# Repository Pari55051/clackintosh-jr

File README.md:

# Clackintosh Jr.
A macropad to accompany my mac and my keyboard 'Clackintosh'

## Features
- 8 mechanical keys
- Rotary encoder for volume up/down _ its switch as mute button
- 0.91" SSD1306 OLED display
- per-key RGB light
- Xiao RP2040 and KMK firmware

Each key launches a different app on macOS, the rotary encoder controls volume, and the OLED provides live feedback.

## Screenshots

## BOM

| Item                               | Qty |
|------------------------------------|-----|
| Seeed Xiao RP2040                  | 1   |
| Mechanical switches                | 8   |
| Keycaps                            | 8   |
| EC11Rotary Encoder                 | 1   |
| 0.91" OLED display                 | 1   |
| Diodes (for matrix)                | 9   |
| PCB                                | 1   |
| 3D printed case (top + bottom)     | 1   |
| Screws (case)                      | 4   |

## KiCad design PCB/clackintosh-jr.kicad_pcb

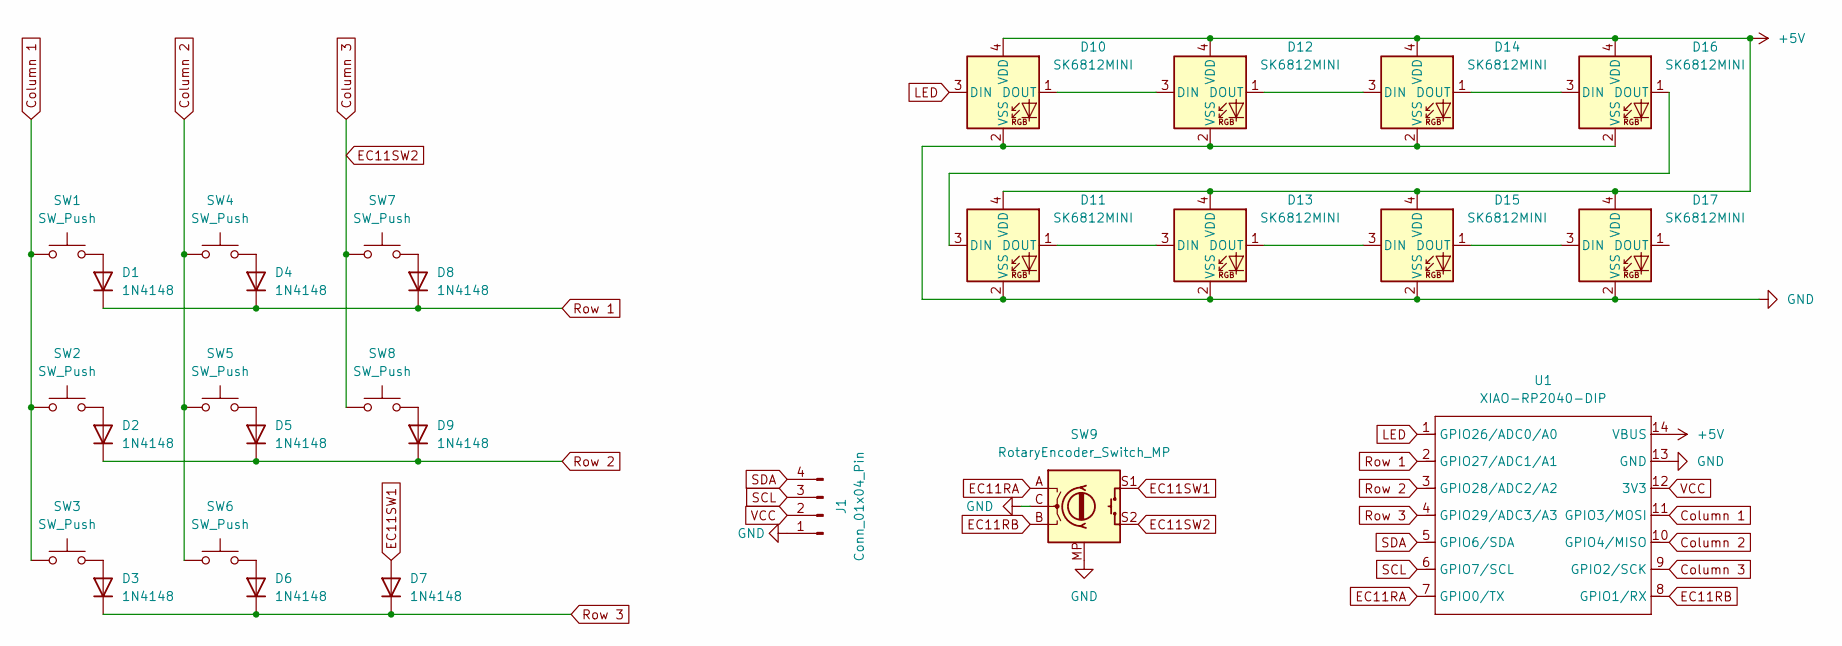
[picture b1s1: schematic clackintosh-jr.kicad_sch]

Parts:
D1, D2, D3, D4, D5, D6, D7, D8, D9: 1N4148; D_DO-35_SOD27_P7.62mm_Horizontal
D10, D11, D12, D13, D14, D15, D16, D17: SK6812MINI; SK6812-MINI-E
J1: Conn_01x04_Pin; SSD1306-0.91-OLED-4pin-128x32
SW1, SW2, SW3, SW4, SW5, SW6, SW7, SW8: SW_Push; SW_Cherry_MX_1.00u_PCB
SW9: RotaryEncoder_Switch_MP; RotaryEncoder_Alps_EC11E-Switch_Vertical_H20mm
U1: XIAO-RP2040-DIP

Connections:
+5V: D10.4 (VDD), D11.4 (VDD), D12.4 (VDD), D13.4 (VDD), D14.4 (VDD), D15.4 (VDD), D16.4 (VDD), D17.4 (VDD), U1.14 (VBUS)
Column 1: SW1.1, SW2.1, SW3.1, U1.11 (GPIO3/MOSI)
Column 2: SW4.1, SW5.1, SW6.1, U1.10 (GPIO4/MISO)
Column 3: SW7.1, SW8.1, SW9.S2, U1.9 (GPIO2/SCK)
EC11RA: SW9.A, U1.7 (GPIO0/TX)
EC11RB: SW9.B, U1.8 (GPIO1/RX)
EC11SW1: D7.2 (A), SW9.S1
GND: D10.2 (VSS), D11.2 (VSS), D12.2 (VSS), D13.2 (VSS), D14.2 (VSS), D15.2 (VSS), D16.2 (VSS), D17.2 (VSS), J1.1, SW9.C, SW9.MP, U1.13 (GND)
LED: D10.3 (DIN), U1.1 (GPIO26/ADC0/A0)
unnamed: D1.2 (A), SW1.2
unnamed: D2.2 (A), SW2.2
unnamed: D3.2 (A), SW3.2
unnamed: D4.2 (A), SW4.2
unnamed: D5.2 (A), SW5.2
unnamed: D6.2 (A), SW6.2
unnamed: D8.2 (A), SW7.2
unnamed: D9.2 (A), SW8.2
unnamed: D10.1 (DOUT), D12.3 (DIN)
unnamed: D11.3 (DIN), D16.1 (DOUT)
unnamed: D11.1 (DOUT), D13.3 (DIN)
unnamed: D12.1 (DOUT), D14.3 (DIN)
unnamed: D13.1 (DOUT), D15.3 (DIN)
unnamed: D14.1 (DOUT), D16.3 (DIN)
unnamed: D15.1 (DOUT), D17.3 (DIN)
Row 1: D1.1 (K), D4.1 (K), D8.1 (K), U1.2 (GPIO27/ADC1/A1)
Row 2: D2.1 (K), D5.1 (K), D9.1 (K), U1.3 (GPIO28/ADC2/A2)
Row 3: D3.1 (K), D6.1 (K), D7.1 (K), U1.4 (GPIO29/ADC3/A3)
SCL: J1.3, U1.6 (GPIO7/SCL)
SDA: J1.4, U1.5 (GPIO6/SDA)
VCC: J1.2, U1.12 (3V3)

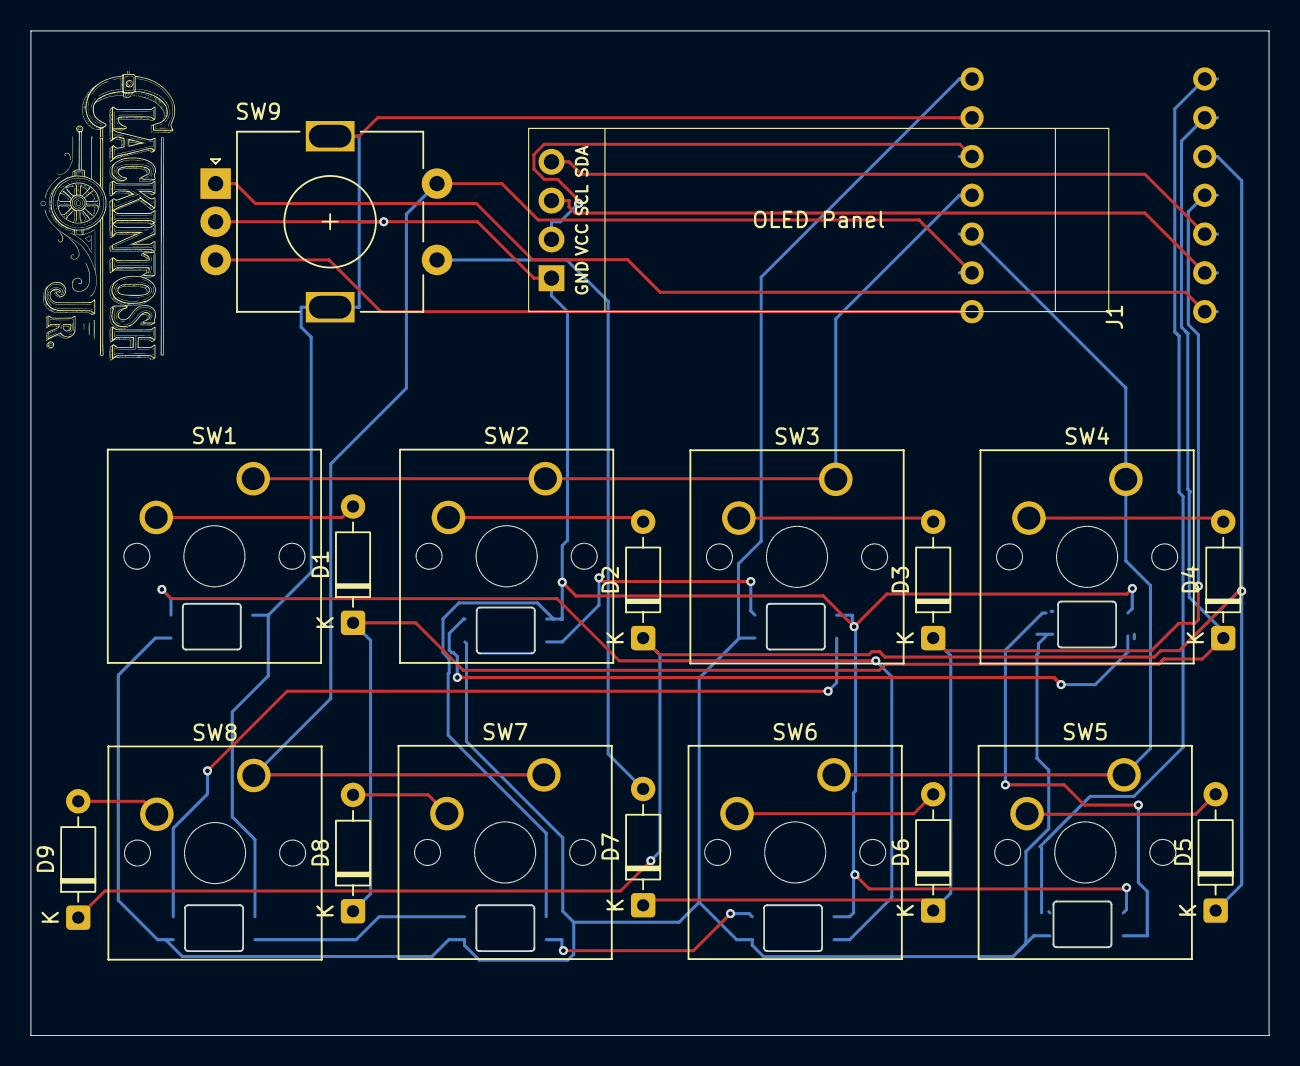
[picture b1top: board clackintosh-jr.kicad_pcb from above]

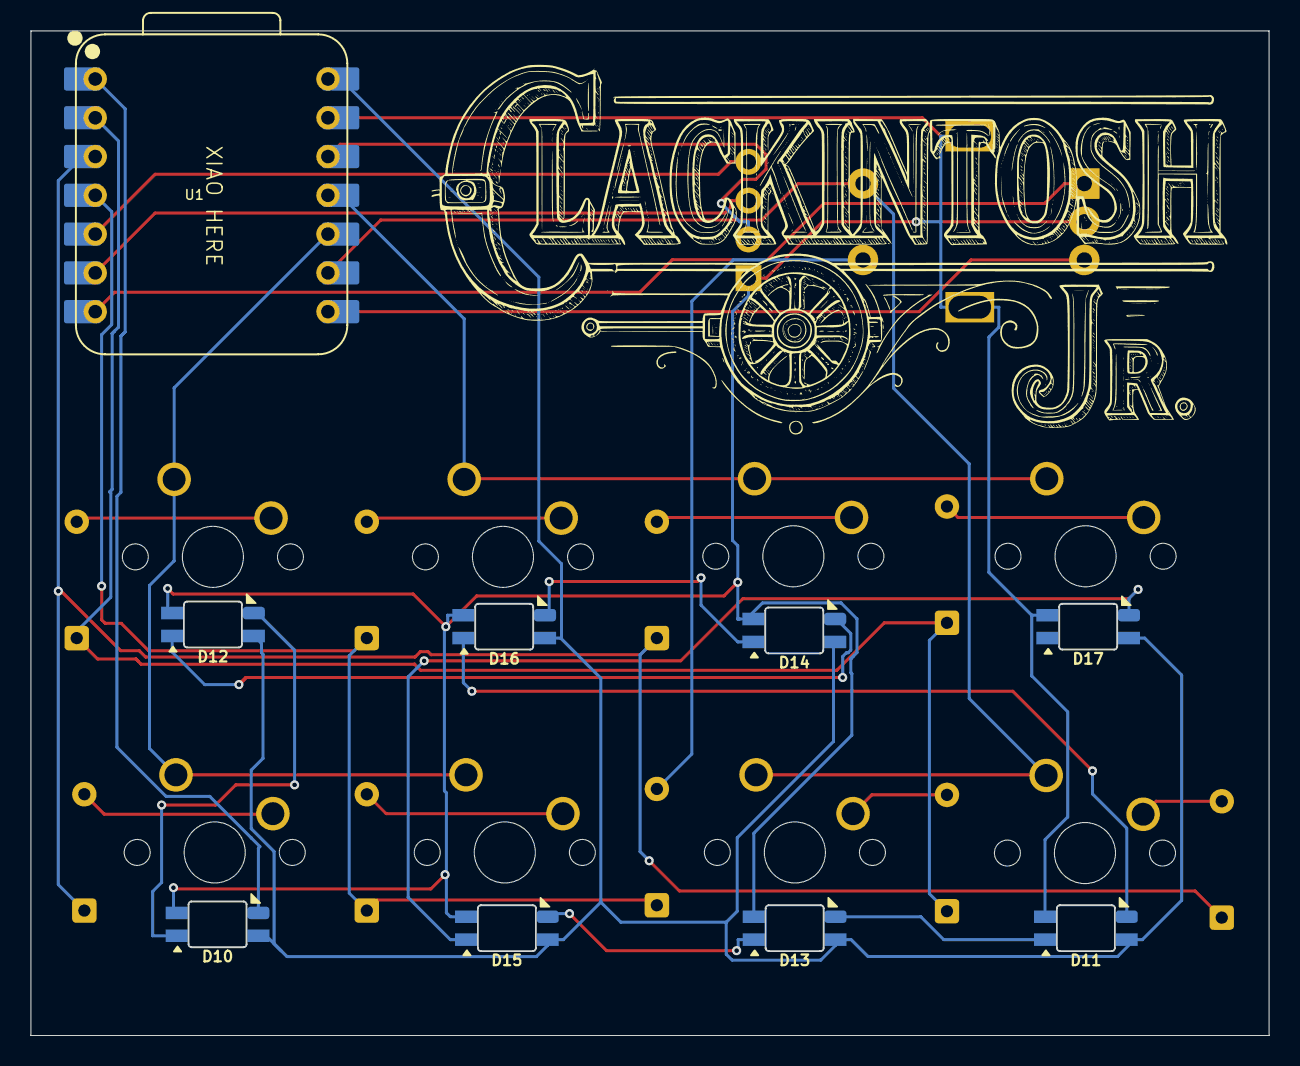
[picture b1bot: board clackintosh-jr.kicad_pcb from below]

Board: 2 copper layers, 81.0 x 65.7 mm, 28 parts (9 on the bottom side), 30 nets.

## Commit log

2025-07-18 case done + minor updates to pcb
2025-07-19 firmware done
2025-07-19 update readme + production folder
